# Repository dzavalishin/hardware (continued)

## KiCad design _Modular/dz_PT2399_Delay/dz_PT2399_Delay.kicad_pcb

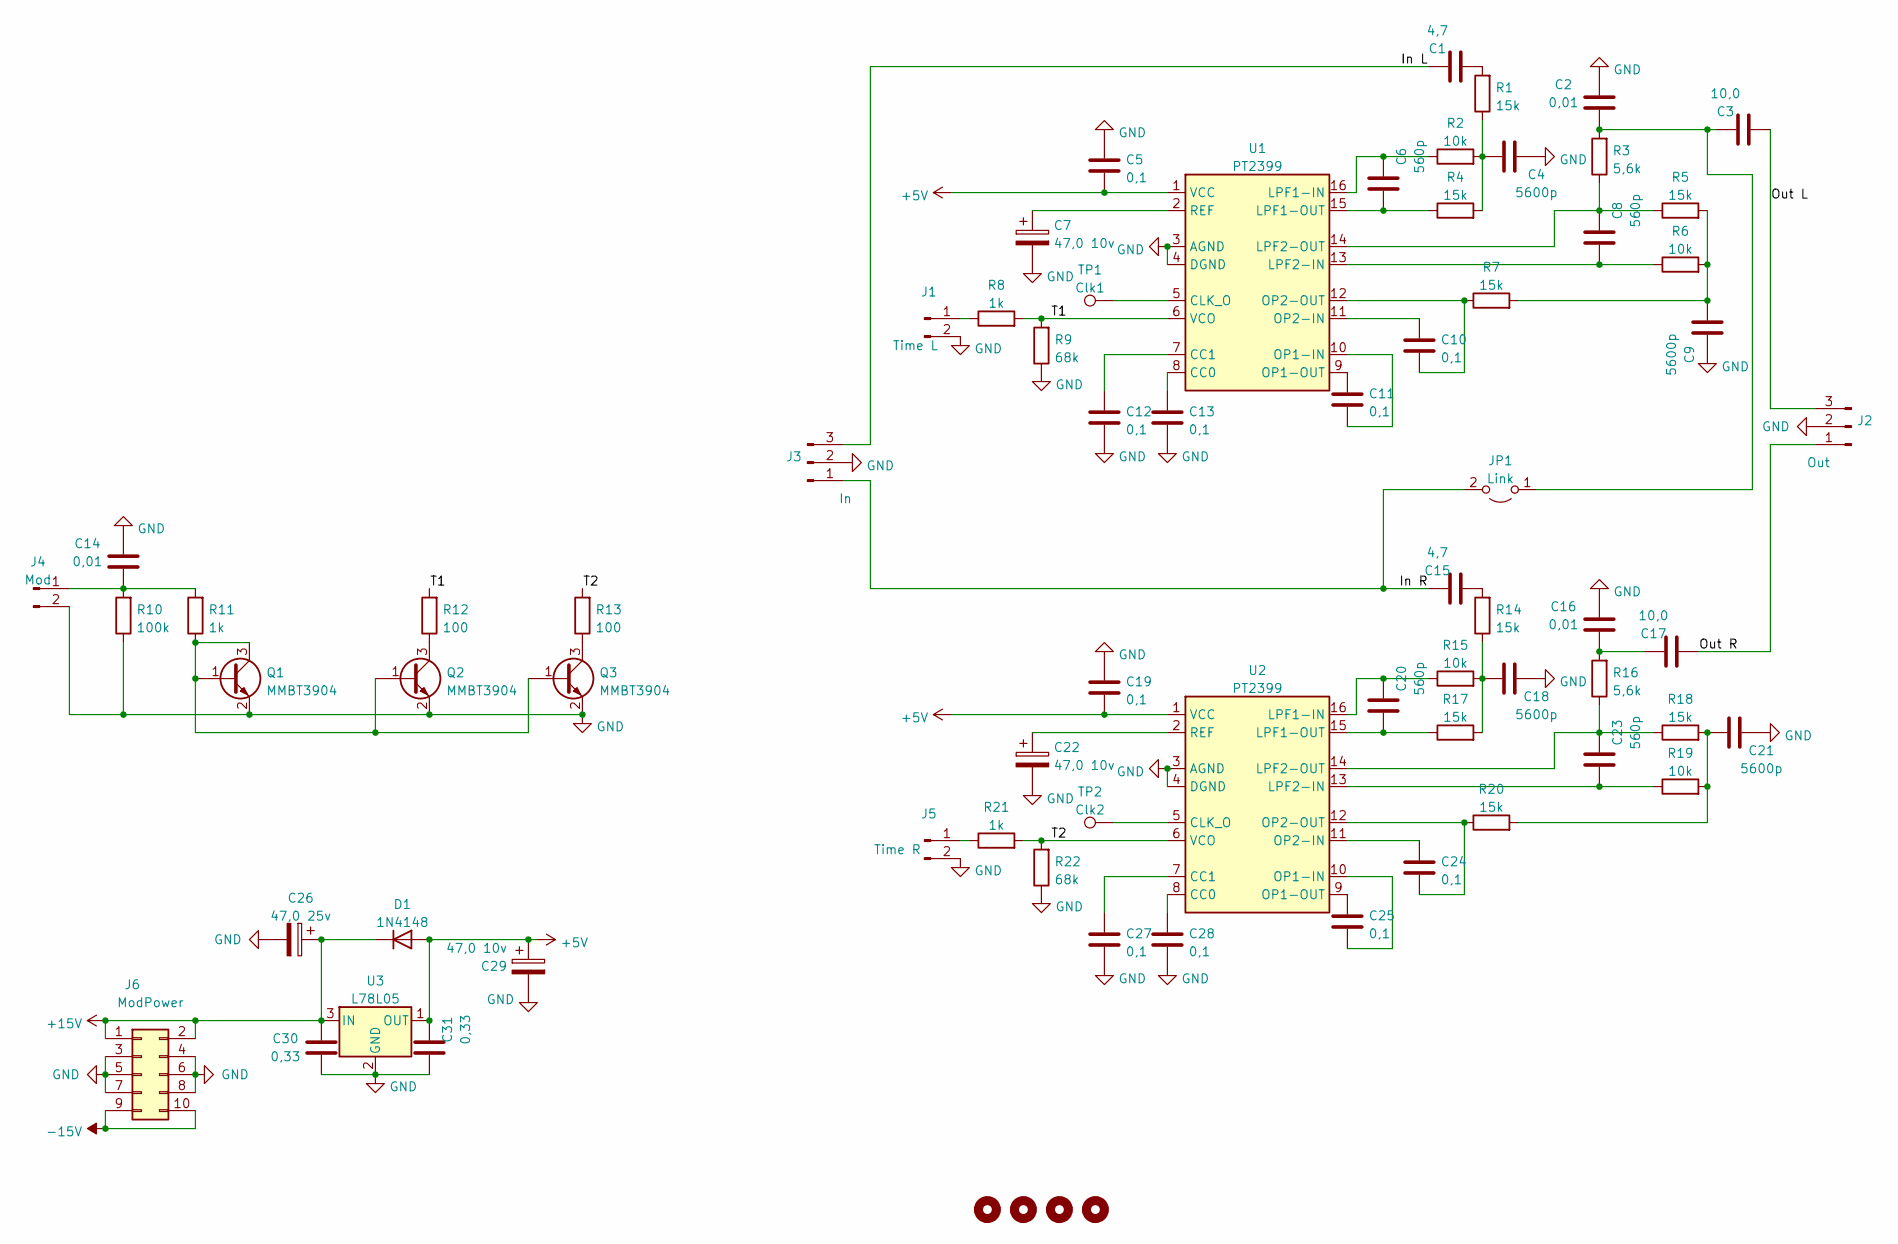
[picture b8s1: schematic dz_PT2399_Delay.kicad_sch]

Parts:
C1, C15: 4,7; C_0805_2012Metric_Pad1.18x1.45mm_HandSolder
C2, C14, C16: 0,01; C_0805_2012Metric_Pad1.18x1.45mm_HandSolder
C3, C17: 10,0; C_0805_2012Metric_Pad1.18x1.45mm_HandSolder
C4, C9, C18, C21: 5600p; C_Disc_D5.0mm_W2.5mm_P2.50mm
C5, C10, C11, C12, C13, C19, C24, C25, C27, C28: 0,1; C_1206_3216Metric_Pad1.33x1.80mm_HandSolder
C6, C8, C20, C23: 560p; C_Disc_D5.0mm_W2.5mm_P2.50mm
C7, C22, C29: 47,0 10v; CP_Radial_D5.0mm_P2.50mm
C26: 47,0 25v; CP_Radial_D5.0mm_P2.50mm
C30, C31: 0,33; C_0805_2012Metric_Pad1.18x1.45mm_HandSolder
D1: 1N4148; D_MiniMELF
H1, H2, H3, H4: MountingHole; MountingHole_3.2mm_M3
J1: Time L; PinHeader_1x02_P2.54mm_Vertical
J2: Out; PinHeader_1x03_P2.54mm_Vertical
J3: In; PinHeader_1x03_P2.54mm_Vertical
J4: Mod; PinHeader_1x02_P2.54mm_Vertical
J5: Time R; PinHeader_1x02_P2.54mm_Vertical
J6: ModPower; PinHeader_2x05_P2.54mm_Vertical
JP1: Link; PinHeader_1x02_P2.54mm_Vertical
Q1, Q2, Q3: MMBT3904; SOT-23
R1, R4, R5, R7, R14, R17, R18, R20: 15k; R_1206_3216Metric_Pad1.30x1.75mm_HandSolder
R2, R6, R15, R19: 10k; R_1206_3216Metric_Pad1.30x1.75mm_HandSolder
R3, R16: 5,6k; R_1206_3216Metric_Pad1.30x1.75mm_HandSolder
R8, R11, R21: 1k; R_1206_3216Metric_Pad1.30x1.75mm_HandSolder
R9, R22: 68k; R_1206_3216Metric_Pad1.30x1.75mm_HandSolder
R10: 100k; R_1206_3216Metric_Pad1.30x1.75mm_HandSolder
R12, R13: 100; R_1206_3216Metric_Pad1.30x1.75mm_HandSolder
TP1: Clk1; PinHeader_1x01_P2.54mm_Vertical
TP2: Clk2; PinHeader_1x01_P2.54mm_Vertical
U1, U2: PT2399; DIP-16_W7.62mm_Socket_LongPads
U3: L78L05; SOT-89-3

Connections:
+5V: C5.2, C19.2, C29.1, C31.2, D1.2 (A), U1.1 (VCC), U2.1 (VCC), U3.1 (OUT)
+15V: C26.1, C30.2, D1.1 (K), J6.1, J6.2, U3.3 (IN)
-15V: J6.9, J6.10
/In L: C1.2, J3.3
/In R: C15.2, J3.1, JP1.2 (B)
/Out L: C3.1, J2.3
/Out R: C17.1, J2.1
/T1: R8.2, R9.2, R12.2, U1.6 (VCO)
/T2: R13.2, R21.2, R22.2, U2.6 (VCO)
GND: C2.2, C4.2, C5.1, C7.2, C9.2, C12.2, C13.2, C14.2, C16.2, C18.2, C19.1, C21.2, C22.2, C26.2, C27.2, C28.2, C29.2, C30.1, C31.1, J1.2, J2.2, J4.2, J5.2, J6.3, J6.4, J6.5, J6.6, J6.7, J6.8, Q1.2 (E), Q2.2 (E), Q3.2 (E), R9.1, R10.1, R22.1, U1.3 (AGND), U1.4 (DGND), U2.3 (AGND), U2.4 (DGND), U3.2 (GND)
unnamed: C1.1, R1.2
unnamed: C2.1, C3.2, JP1.1 (A), R3.2
unnamed: C4.1, R1.1, R2.2, R4.2
unnamed: C6.1, R4.1, U1.15 (LPF1-OUT)
unnamed: C6.2, R2.1, U1.16 (LPF1-IN)
unnamed: C7.1, U1.2 (REF)
unnamed: C8.1, R6.1, U1.13 (LPF2-IN)
unnamed: C8.2, R3.1, R5.1, U1.14 (LPF2-OUT)
unnamed: C9.1, R5.2, R6.2, R7.2
unnamed: C10.1, R7.1, U1.12 (OP2-OUT)
unnamed: C10.2, U1.11 (OP2-IN)
unnamed: C11.1, U1.10 (OP1-IN)
unnamed: C11.2, U1.9 (OP1-OUT)
unnamed: C12.1, U1.7 (CC1)
unnamed: C13.1, U1.8 (CC0)
unnamed: C14.1, J4.1, R10.2, R11.2
unnamed: C15.1, R14.2
unnamed: C16.1, C17.2, R16.2
unnamed: C18.1, R14.1, R15.2, R17.2
unnamed: C20.1, R17.1, U2.15 (LPF1-OUT)
unnamed: C20.2, R15.1, U2.16 (LPF1-IN)
unnamed: C21.1, R18.2, R19.2, R20.2
unnamed: C22.1, U2.2 (REF)
unnamed: C23.1, R19.1, U2.13 (LPF2-IN)
unnamed: C23.2, R16.1, R18.1, U2.14 (LPF2-OUT)
unnamed: C24.1, R20.1, U2.12 (OP2-OUT)
unnamed: C24.2, U2.11 (OP2-IN)
unnamed: C25.1, U2.10 (OP1-IN)
unnamed: C25.2, U2.9 (OP1-OUT)
unnamed: C27.1, U2.7 (CC1)
unnamed: C28.1, U2.8 (CC0)
unnamed: J1.1, R8.1
unnamed: J5.1, R21.1
unnamed: Q1.1 (B), Q1.3 (C), Q2.1 (B), Q3.1 (B), R11.1
unnamed: Q2.3 (C), R12.1
unnamed: Q3.3 (C), R13.1
unnamed: TP1.1, U1.5 (CLK_O)
unnamed: TP2.1, U2.5 (CLK_O)

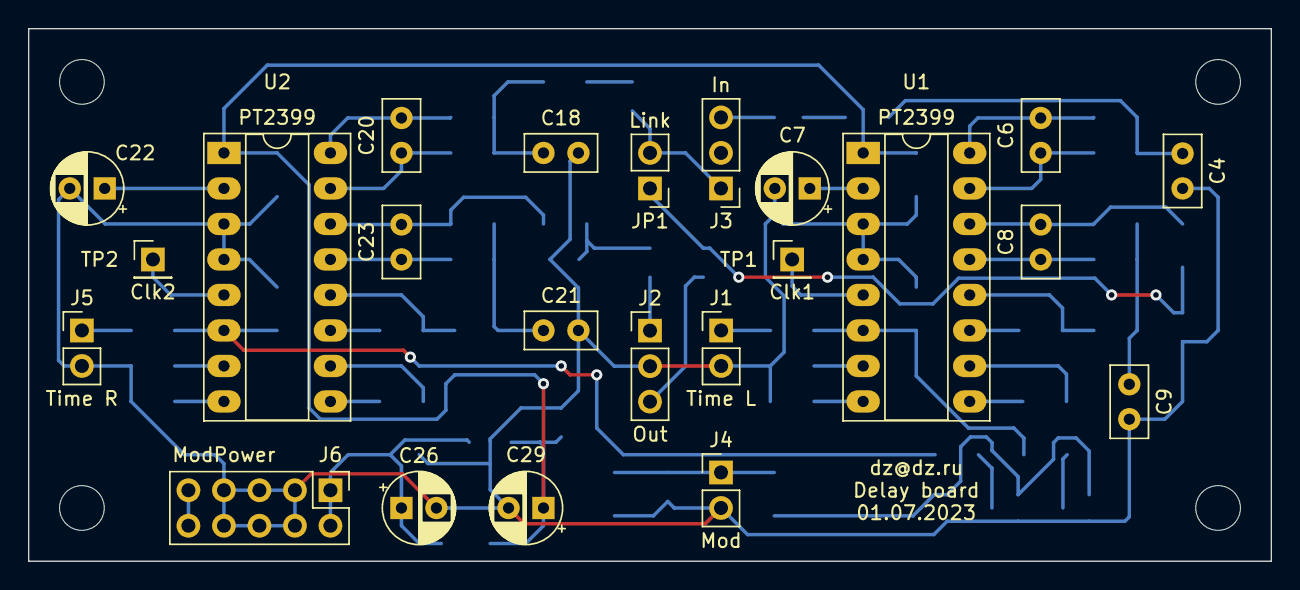
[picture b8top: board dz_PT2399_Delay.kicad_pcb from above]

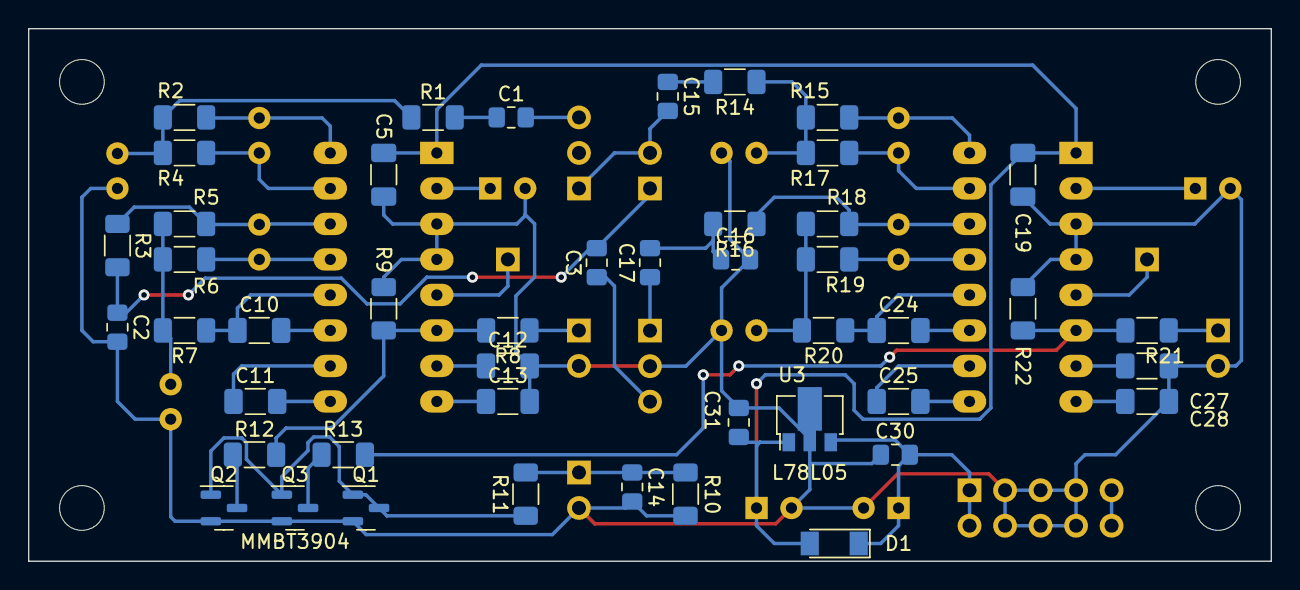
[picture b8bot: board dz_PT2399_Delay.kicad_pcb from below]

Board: 2 copper layers, 88.9 x 38.1 mm, 73 parts (46 on the bottom side), 48 nets.
